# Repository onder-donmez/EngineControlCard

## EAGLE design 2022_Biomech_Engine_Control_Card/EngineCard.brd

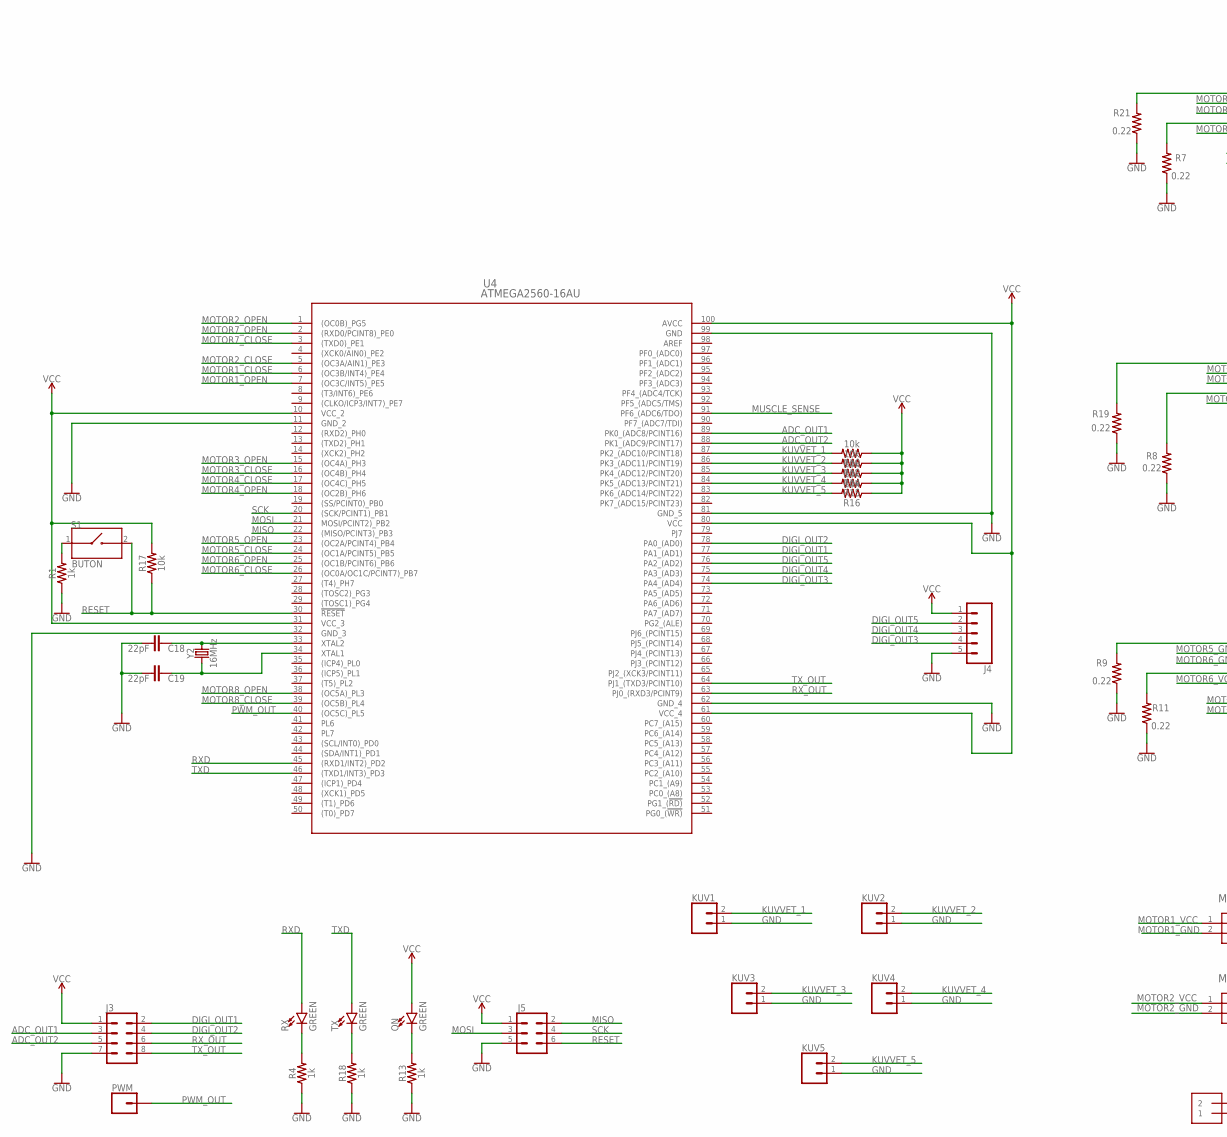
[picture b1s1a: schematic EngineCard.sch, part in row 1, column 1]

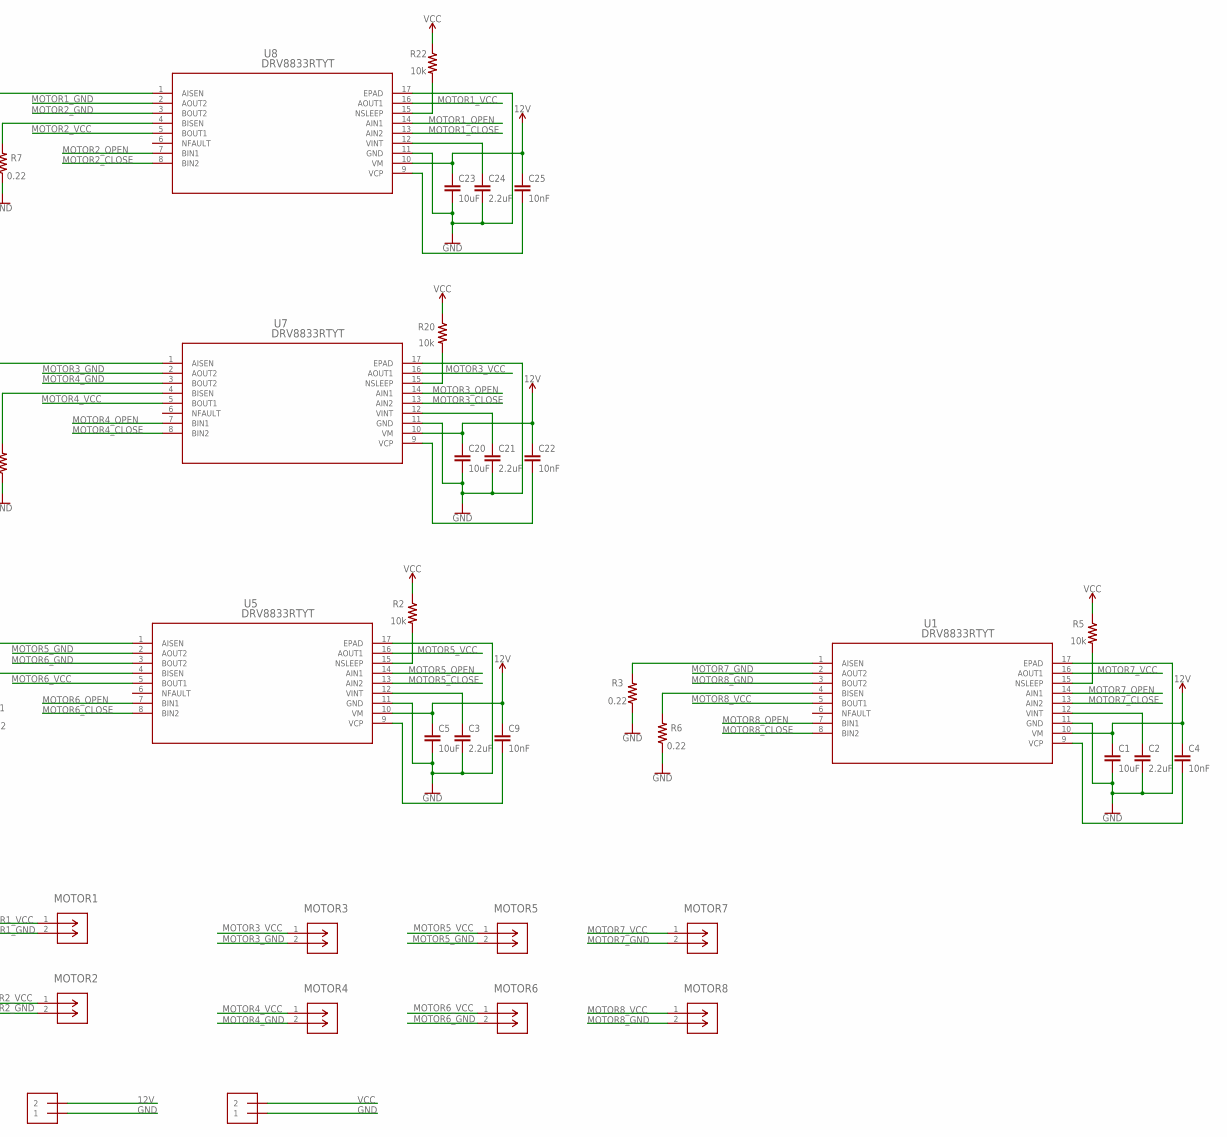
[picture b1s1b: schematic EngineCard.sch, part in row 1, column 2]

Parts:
C1, C5, C20, C23: 10uF; 0603
C2, C3, C21, C24: 2.2uF; 0603
C4, C9, C22, C25: 10nF; 0603
C18, C19: 22pF; 0603
J3: CONN_04X2; 2X4
J4: CONN_05NO_SILK; 1X05_NO_SILK
J5: CONN_03X2NO_SILK; 2X3-NS
KUV1, KUV2, KUV3, KUV4, KUV5: CONN_02; 1X02
MOTOR1, MOTOR2, MOTOR3, MOTOR4, MOTOR5, MOTOR6, MOTOR7, MOTOR8: 530470210; CON_530470210_MOL
ON: GREEN; LED-0603
PIL: 1X2-3.5MM
PWM: CONN_01; 1X01
R1, R4, R13, R18: 1k; 0603
R2, R5, R10, R12, R14, R15, R16, R17, R20, R22: 10k; 0603
R3, R6, R7, R8, R9, R11, R19, R21: 0.22; 0805
REG: 1X2-3.5MM
RX: GREEN; LED-0603
S1: BUTON; SW_1437566-4
TX: GREEN; LED-0603
U1, U5, U7, U8: DRV8833RTYT; RTY16
U4: ATMEGA2560-16AU; 100A_ATM
Y2: 16MHz; HC49US

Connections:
12V: C1.1, C4.1, C5.1, C9.1, C20.1, C22.1, C23.1, C25.1, PIL.2, U1.10 (VM), U5.10 (VM), U7.10 (VM), U8.10 (VM)
ADC_OUT1: J3.3, U4.89 (PK0_(ADC8/PCINT16))
ADC_OUT2: J3.5, U4.88 (PK1_(ADC9/PCINT17))
AREF: U4.98 (AREF)
DIGI_OUT1: J3.2, U4.77 (PA1_(AD1))
DIGI_OUT2: J3.4, U4.78 (PA0_(AD0))
DIGI_OUT3: J4.4, U4.74 (PA4_(AD4))
DIGI_OUT4: J4.3, U4.75 (PA3_(AD3))
DIGI_OUT5: J4.2, U4.76 (PA2_(AD2))
GND: C1.2, C2.2, C3.2, C5.2, C18.2, C19.2, C20.2, C21.2, C23.2, C24.2, J3.7, J4.5, J5.5, KUV1.1, KUV2.1, KUV3.1, KUV4.1, KUV5.1, PIL.1, R1.1, R3.1, R4.1, R6.1, R7.1, R8.1, R9.1, R11.1, R13.1, R18.1, R19.1, R21.1, REG.1, U1.11 (GND), U1.17 (EPAD), U4.11 (GND_2), U4.32 (GND_3), U4.62 (GND_4), U4.81 (GND_5), U4.99 (GND), U5.11 (GND), U5.17 (EPAD), U7.11 (GND), U7.17 (EPAD), U8.11 (GND), U8.17 (EPAD)
KUVVET_1: KUV1.2, R10.2, U4.87 (PK2_(ADC10/PCINT18))
KUVVET_2: KUV2.2, R12.2, U4.86 (PK3_(ADC11/PCINT19))
KUVVET_3: KUV3.2, R14.2, U4.85 (PK4_(ADC12/PCINT20))
KUVVET_4: KUV4.2, R15.2, U4.84 (PK5_(ADC13/PCINT21))
KUVVET_5: KUV5.2, R16.2, U4.83 (PK6_(ADC14/PCINT22))
MISO: J5.2, U4.22 ((MISO/PCINT3)_PB3)
MOSI: J5.3, U4.21 (MOSI/PCINT2)_PB2)
MOTOR1_CLOSE: U4.6 ((OC3B/INT4)_PE4), U8.13 (AIN2)
MOTOR1_GND: MOTOR1.2, U8.2 (AOUT2)
MOTOR1_OPEN: U4.7 ((OC3C/INT5)_PE5), U8.14 (AIN1)
MOTOR1_VCC: MOTOR1.1, U8.16 (AOUT1)
MOTOR2_CLOSE: U4.5 ((OC3A/AIN1)_PE3), U8.8 (BIN2)
MOTOR2_GND: MOTOR2.2, U8.3 (BOUT2)
MOTOR2_OPEN: U4.1 ((OC0B)_PG5), U8.7 (BIN1)
MOTOR2_VCC: MOTOR2.1, U8.5 (BOUT1)
MOTOR3_CLOSE: U4.16 ((OC4B)_PH4), U7.13 (AIN2)
MOTOR3_GND: MOTOR3.2, U7.2 (AOUT2)
MOTOR3_OPEN: U4.15 ((OC4A)_PH3), U7.14 (AIN1)
MOTOR3_VCC: MOTOR3.1, U7.16 (AOUT1)
MOTOR4_CLOSE: U4.17 ((OC4C)_PH5), U7.8 (BIN2)
MOTOR4_GND: MOTOR4.2, U7.3 (BOUT2)
MOTOR4_OPEN: U4.18 ((OC2B)_PH6), U7.7 (BIN1)
MOTOR4_VCC: MOTOR4.1, U7.5 (BOUT1)
MOTOR5_CLOSE: U4.24 ((OC1A/PCINT5)_PB5), U5.13 (AIN2)
MOTOR5_GND: MOTOR5.2, U5.2 (AOUT2)
MOTOR5_OPEN: U4.23 ((OC2A/PCINT4)_PB4), U5.14 (AIN1)
MOTOR5_VCC: MOTOR5.1, U5.16 (AOUT1)
MOTOR6_CLOSE: U4.26 ((OC0A/OC1C/PCINT7)_PB7), U5.8 (BIN2)
MOTOR6_GND: MOTOR6.2, U5.3 (BOUT2)
MOTOR6_OPEN: U4.25 ((OC1B/PCINT6)_PB6), U5.7 (BIN1)
MOTOR6_VCC: MOTOR6.1, U5.5 (BOUT1)
MOTOR7_CLOSE: U1.13 (AIN2), U4.3 ((TXD0)_PE1)
MOTOR7_GND: MOTOR7.2, U1.2 (AOUT2)
MOTOR7_OPEN: U1.14 (AIN1), U4.2 ((RXD0/PCINT8)_PE0)
MOTOR7_VCC: MOTOR7.1, U1.16 (AOUT1)
MOTOR8_CLOSE: U1.8 (BIN2), U4.39 ((OC5B)_PL4)
MOTOR8_GND: MOTOR8.2, U1.3 (BOUT2)
MOTOR8_OPEN: U1.7 (BIN1), U4.38 ((OC5A)_PL3)
MOTOR8_VCC: MOTOR8.1, U1.5 (BOUT1)
MUSCLE_SENSE: U4.91 (PF6_(ADC6/TDO))
unnamed: R9.2, U5.1 (AISEN)
unnamed: R1.2, S1.1
unnamed: R2.2, U5.15 (NSLEEP)
unnamed: C4.2, U1.9 (VCP)
unnamed: R3.2, U1.1 (AISEN)
unnamed: C2.1, U1.12 (VINT)
unnamed: R5.2, U1.15 (NSLEEP)
unnamed: C9.2, U5.9 (VCP)
unnamed: R6.2, U1.4 (BISEN)
unnamed: R7.2, U8.4 (BISEN)
unnamed: R8.2, U7.4 (BISEN)
unnamed: C3.1, U5.12 (VINT)
unnamed: R11.2, U5.4 (BISEN)
unnamed: R4.2, RX.C
unnamed: ON.C, R13.2
unnamed: R18.2, TX.C
unnamed: C18.1, U4.33 (XTAL2), Y2.2
unnamed: C19.1, U4.34 (XTAL1), Y2.1
unnamed: C22.2, U7.9 (VCP)
unnamed: R19.2, U7.1 (AISEN)
unnamed: C21.1, U7.12 (VINT)
unnamed: R20.2, U7.15 (NSLEEP)
unnamed: C25.2, U8.9 (VCP)
unnamed: R21.2, U8.1 (AISEN)
unnamed: C24.1, U8.12 (VINT)
unnamed: R22.2, U8.15 (NSLEEP)
PWM_OUT: PWM.1, U4.40 ((OC5C)_PL5)
RESET: J5.6, R17.1, S1.2, U4.30 (!RESET)
RXD: RX.A, U4.45 ((RXD1/INT2)_PD2)
RX_OUT: J3.6, U4.63 (PJ0_(RXD3/PCINT9))
SCK: J5.4, U4.20 ((SCK/PCINT1)_PB1)
TXD: TX.A, U4.46 ((TXD1/INT3)_PD3)
TX_OUT: J3.8, U4.64 (PJ1_(TXD3/PCINT10))
VCC: J3.1, J4.1, J5.1, ON.A, R2.1, R5.1, R10.1, R12.1, R14.1, R15.1, R16.1, R17.2, R20.1, R22.1, REG.2, U4.10 (VCC_2), U4.31 (VCC_3), U4.61 (VCC_4), U4.80 (VCC), U4.100 (AVCC)

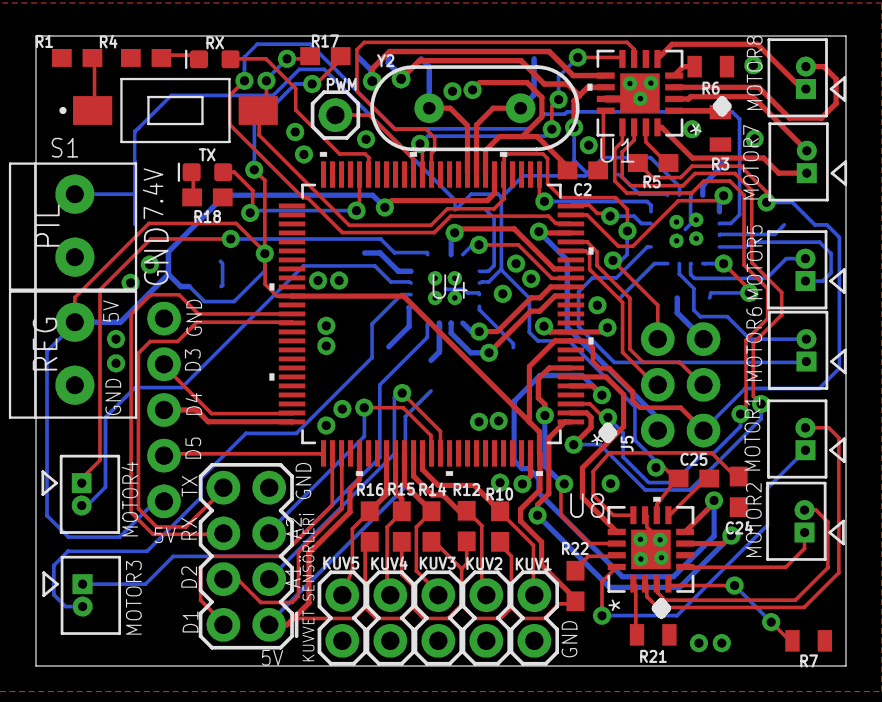
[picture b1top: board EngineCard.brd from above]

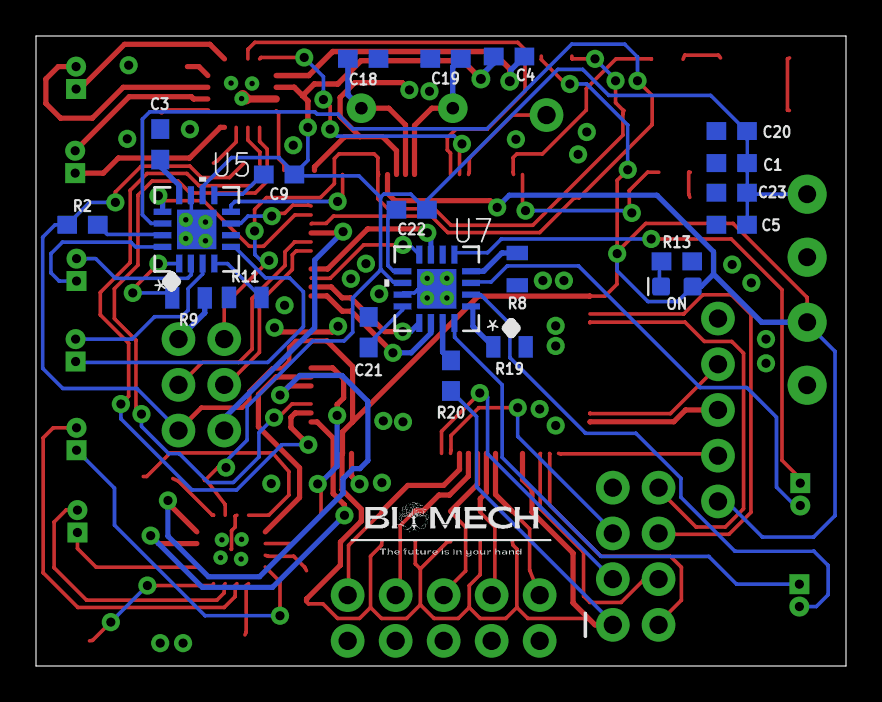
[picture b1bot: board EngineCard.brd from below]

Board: 2 copper layers, 45.0 x 35.0 mm, 65 parts (21 on the bottom side), 82 nets.

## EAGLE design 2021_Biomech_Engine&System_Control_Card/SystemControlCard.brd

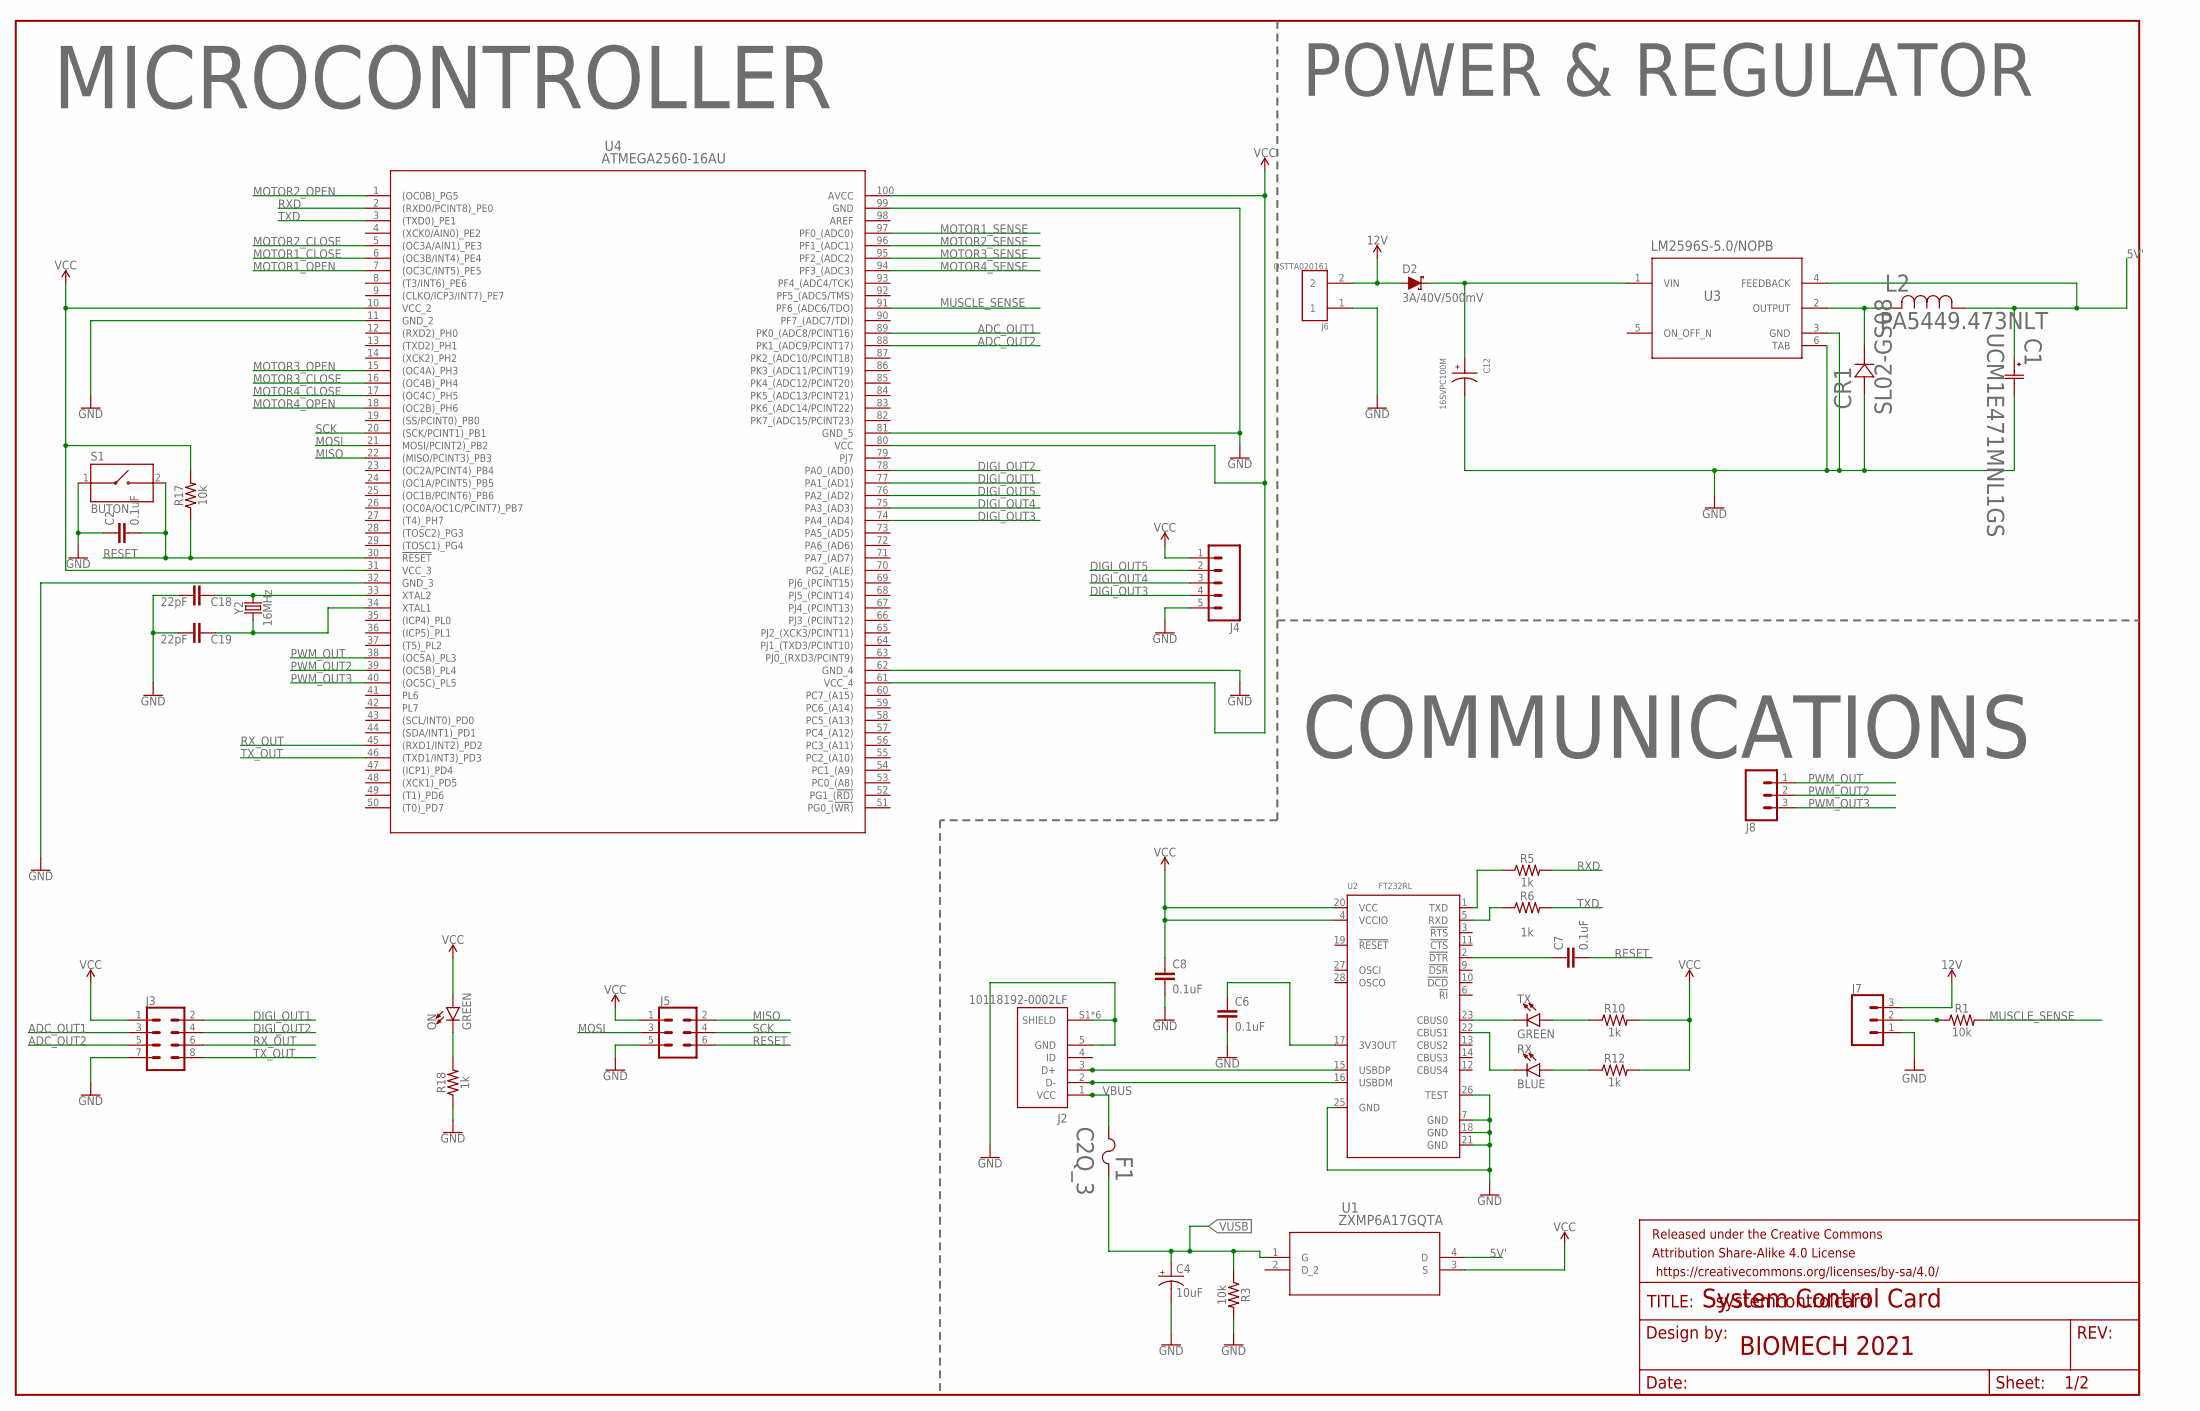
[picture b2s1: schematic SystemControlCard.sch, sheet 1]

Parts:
C1: UCM1E471MNL1GS; CAP_UCD_8X10_NCH
C2, C6, C7, C8: 0.1uF; 0603
C4: 10uF; EIA3216
C12: 16SVPC100M; CAP_16SVPC100M
C18, C19: 22pF; 0603
CR1: SL02-GS08; DIODE_SL02-GS08_VIS
D2: 3A/40V/500mV; SMA-DIODE
F1: C2Q_3; C2_BEL
FRAME2: FRAME-LEDGER; CREATIVE_COMMONS
J2: 10118192-0002LF; AMPHENOL_10118192-0002LF
J3: CONN_04X2; 2X4
J4: CONN_05NO_SILK; 1X05_NO_SILK
J5: CONN_03X2NO_SILK; 2X3-NS
J6: OSTTA020161; OST_OSTTA020161
J7, J8: CONN_031X03_NO_SILK; 1X03_NO_SILK
L2: PA5449.473NLT; IND_PA5449.473NLT_PUL
ON: GREEN; LED-0603
R1, R3, R17: 10k; 0603
R5, R6, R10, R12, R18: 1k; 0603
RX: BLUE; LED-0603
S1: BUTON; SW_1437566-4
TX: GREEN; LED-0603
U1: ZXMP6A17GQTA; SOT-223_DIO
U2: FT232RL; SSOP28-0.65-10.2X5.2MM
U3: LM2596S-5.0/NOPB; KTT0005B
U4: ATMEGA2560-16AU; 100A_ATM
Y2: 16MHz; HC49US

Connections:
5V': C1.1, L2.1, U1.4 (D), U3.4 (FEEDBACK)
12V: D2.A, J6.2, J7.3; also elsewhere on the board
ADC_OUT1: J3.3, U4.89 (PK0_(ADC8/PCINT16))
ADC_OUT2: J3.5, U4.88 (PK1_(ADC9/PCINT17))
AREF: U4.98 (AREF)
DIGI_OUT1: J3.2, U4.77 (PA1_(AD1))
DIGI_OUT2: J3.4, U4.78 (PA0_(AD0))
DIGI_OUT3: J4.4, U4.74 (PA4_(AD4))
DIGI_OUT4: J4.3, U4.75 (PA3_(AD3))
DIGI_OUT5: J4.2, U4.76 (PA2_(AD2))
GND: C1.2, C2.1, C4.-, C6.2, C8.2, C12.2, C18.2, C19.2, CR1.2, J2.5 (GND), J2.S1 (SHIELD), J2.S2 (SHIELD), J2.S3 (SHIELD), J2.S4 (SHIELD), J2.S5 (SHIELD), J2.S6 (SHIELD), J3.7, J4.5, J5.5, J6.1, J7.1, R3.2, R18.1, S1.1, U2.7 (GND), U2.18 (GND), U2.21 (GND), U2.25 (GND), U2.26 (TEST), U3.3 (GND), U3.6 (TAB), U4.11 (GND_2), U4.32 (GND_3), U4.62 (GND_4), U4.81 (GND_5), U4.99 (GND); also elsewhere on the board
MISO: J5.2, U4.22 ((MISO/PCINT3)_PB3)
MOSI: J5.3, U4.21 (MOSI/PCINT2)_PB2)
MOTOR1_CLOSE: U4.6 ((OC3B/INT4)_PE4); also elsewhere on the board
MOTOR1_OPEN: U4.7 ((OC3C/INT5)_PE5); also elsewhere on the board
MOTOR1_SENSE: U4.97 (PF0_(ADC0)); also elsewhere on the board
MOTOR2_CLOSE: U4.5 ((OC3A/AIN1)_PE3); also elsewhere on the board
MOTOR2_OPEN: U4.1 ((OC0B)_PG5); also elsewhere on the board
MOTOR2_SENSE: U4.96 (PF1_(ADC1)); also elsewhere on the board
MOTOR3_CLOSE: U4.16 ((OC4B)_PH4); also elsewhere on the board
MOTOR3_OPEN: U4.15 ((OC4A)_PH3); also elsewhere on the board
MOTOR3_SENSE: U4.95 (PF2_(ADC2)); also elsewhere on the board
MOTOR4_CLOSE: U4.17 ((OC4C)_PH5); also elsewhere on the board
MOTOR4_OPEN: U4.18 ((OC2B)_PH6); also elsewhere on the board
MOTOR4_SENSE: U4.94 (PF3_(ADC3)); also elsewhere on the board
MUSCLE_SENSE: R1.2, U4.91 (PF6_(ADC6/TDO))
unnamed: C12.1, D2.C, U3.1 (VIN)
unnamed: J2.3 (D+), U2.15 (USBDP)
unnamed: J2.2 (D-), U2.16 (USBDM)
unnamed: R5.1, U2.1 (TXD)
unnamed: R6.1, U2.5 (RXD)
unnamed: C6.1, U2.17 (3V3OUT)
unnamed: TX.C, U2.23 (CBUS0)
unnamed: RX.C, U2.22 (CBUS1)
unnamed: J7.2, R1.1
unnamed: R10.1, TX.A
unnamed: R12.1, RX.A
unnamed: C7.1, U2.2 (!DTR)
unnamed: CR1.1, L2.2, U3.2 (OUTPUT)
unnamed: ON.C, R18.2
unnamed: C18.1, U4.33 (XTAL2), Y2.2
unnamed: C19.1, U4.34 (XTAL1), Y2.1
PWM_OUT: J8.1, U4.38 ((OC5A)_PL3)
PWM_OUT2: J8.2, U4.39 ((OC5B)_PL4)
PWM_OUT3: J8.3, U4.40 ((OC5C)_PL5)
RESET: C2.2, C7.2, J5.6, R17.1, S1.2, U4.30 (!RESET)
RXD: R5.2, U4.2 ((RXD0/PCINT8)_PE0)
RX_OUT: J3.6, U4.45 ((RXD1/INT2)_PD2)
SCK: J5.4, U4.20 ((SCK/PCINT1)_PB1)
TXD: R6.2, U4.3 ((TXD0)_PE1)
TX_OUT: J3.8, U4.46 ((TXD1/INT3)_PD3)
VBUS: F1.1, J2.1 (VCC)
VCC: C8.1, J3.1, J4.1, J5.1, ON.A, R10.2, R12.2, R17.2, U1.3 (S), U2.4 (VCCIO), U2.20 (VCC), U4.10 (VCC_2), U4.31 (VCC_3), U4.61 (VCC_4), U4.80 (VCC), U4.100 (AVCC); also elsewhere on the board
VUSB: C4.+, F1.2, R3.1, U1.1 (G)

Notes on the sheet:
MICROCONTROLLER
POWER & REGULATOR
COMMUNICATIONS

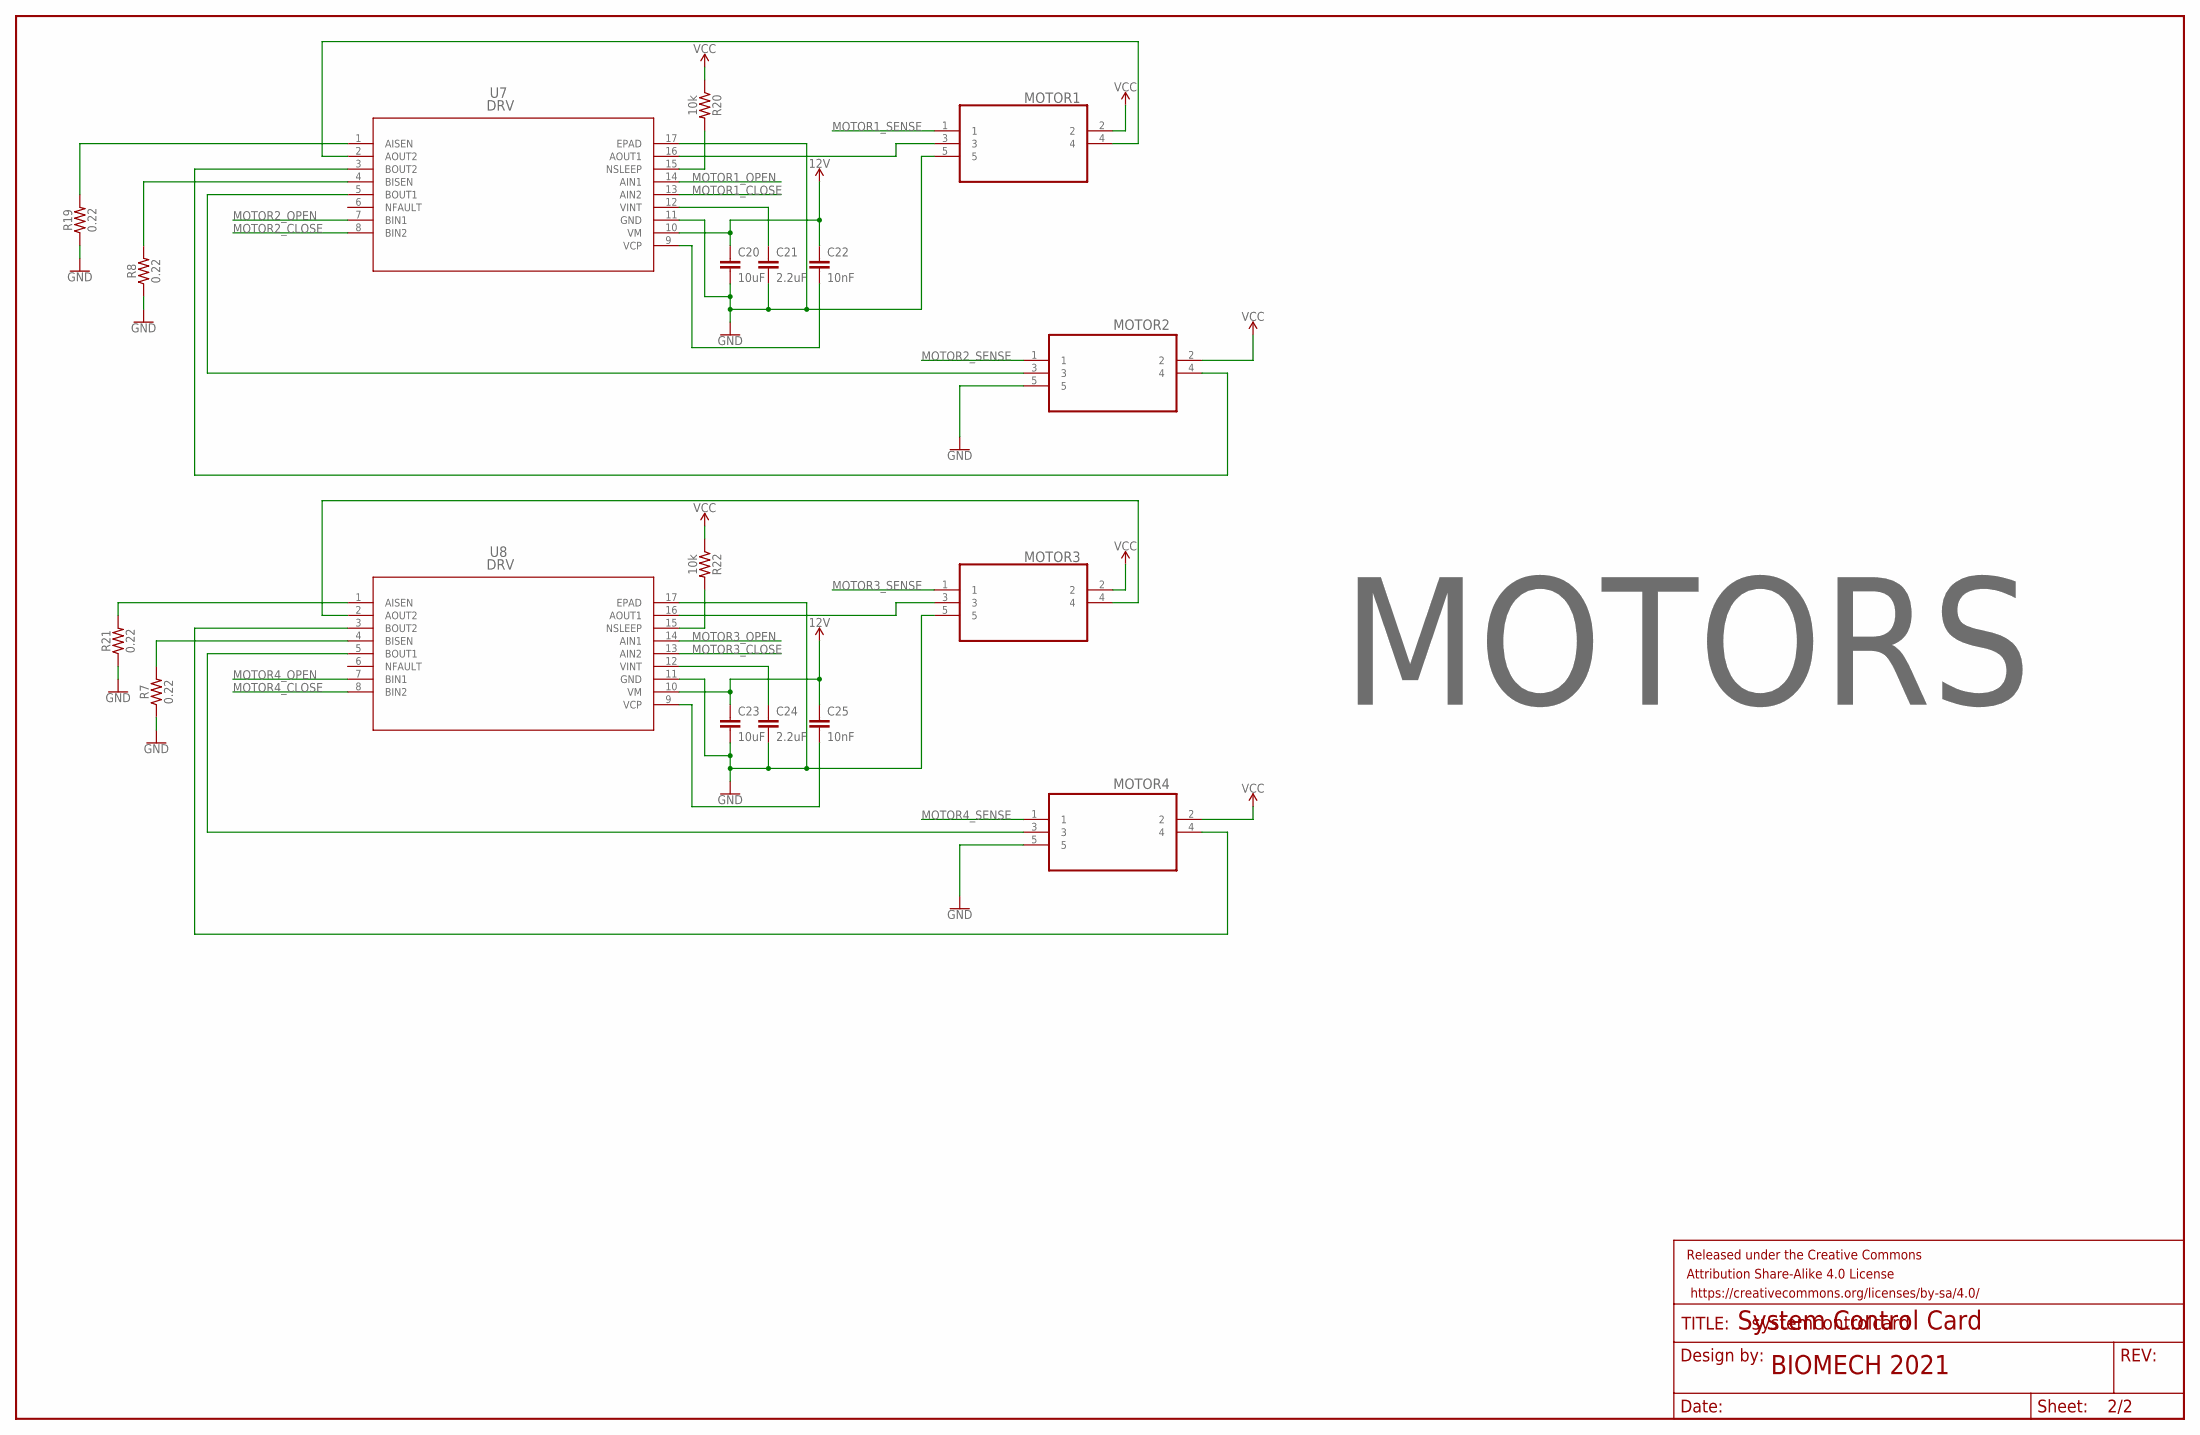
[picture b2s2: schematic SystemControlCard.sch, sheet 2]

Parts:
C20, C23: 10uF; 0603
C21, C24: 2.2uF; 0603
C22, C25: 10nF; 0603
FRAME1: FRAME-LEDGER; CREATIVE_COMMONS
MOTOR1, MOTOR2, MOTOR3, MOTOR4: SFW5R-1STE1LF; FCI_SFW5R-1STE1LF
R7, R8, R19, R21: 0.22; 0805
R20, R22: 10k; 0603
U7, U8: DRV; RTY16

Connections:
12V: C20.1, C22.1, C23.1, C25.1, U7.10 (VM), U8.10 (VM); also elsewhere on the board
GND: C20.2, C21.2, C23.2, C24.2, MOTOR1.5, MOTOR2.5, MOTOR3.5, MOTOR4.5, R7.1, R8.1, R19.1, R21.1, U7.11 (GND), U7.17 (EPAD), U8.11 (GND), U8.17 (EPAD); also elsewhere on the board
MOTOR1_CLOSE: U7.13 (AIN2); also elsewhere on the board
MOTOR1_OPEN: U7.14 (AIN1); also elsewhere on the board
MOTOR1_SENSE: MOTOR1.1; also elsewhere on the board
MOTOR2_CLOSE: U7.8 (BIN2); also elsewhere on the board
MOTOR2_OPEN: U7.7 (BIN1); also elsewhere on the board
MOTOR2_SENSE: MOTOR2.1; also elsewhere on the board
MOTOR3_CLOSE: U8.13 (AIN2); also elsewhere on the board
MOTOR3_OPEN: U8.14 (AIN1); also elsewhere on the board
MOTOR3_SENSE: MOTOR3.1; also elsewhere on the board
MOTOR4_CLOSE: U8.8 (BIN2); also elsewhere on the board
MOTOR4_OPEN: U8.7 (BIN1); also elsewhere on the board
MOTOR4_SENSE: MOTOR4.1; also elsewhere on the board
unnamed: R7.2, U8.4 (BISEN)
unnamed: R8.2, U7.4 (BISEN)
unnamed: C22.2, U7.9 (VCP)
unnamed: R19.2, U7.1 (AISEN)
unnamed: C21.1, U7.12 (VINT)
unnamed: MOTOR2.3, U7.5 (BOUT1)
unnamed: MOTOR1.4, U7.2 (AOUT2)
unnamed: MOTOR2.4, U7.3 (BOUT2)
unnamed: MOTOR1.3, U7.16 (AOUT1)
unnamed: R20.2, U7.15 (NSLEEP)
unnamed: C25.2, U8.9 (VCP)
unnamed: R21.2, U8.1 (AISEN)
unnamed: C24.1, U8.12 (VINT)
unnamed: MOTOR4.3, U8.5 (BOUT1)
unnamed: MOTOR3.4, U8.2 (AOUT2)
unnamed: MOTOR4.4, U8.3 (BOUT2)
unnamed: MOTOR3.3, U8.16 (AOUT1)
unnamed: R22.2, U8.15 (NSLEEP)
VCC: MOTOR1.2, MOTOR2.2, MOTOR3.2, MOTOR4.2, R20.1, R22.1; also elsewhere on the board

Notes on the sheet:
MOTORS

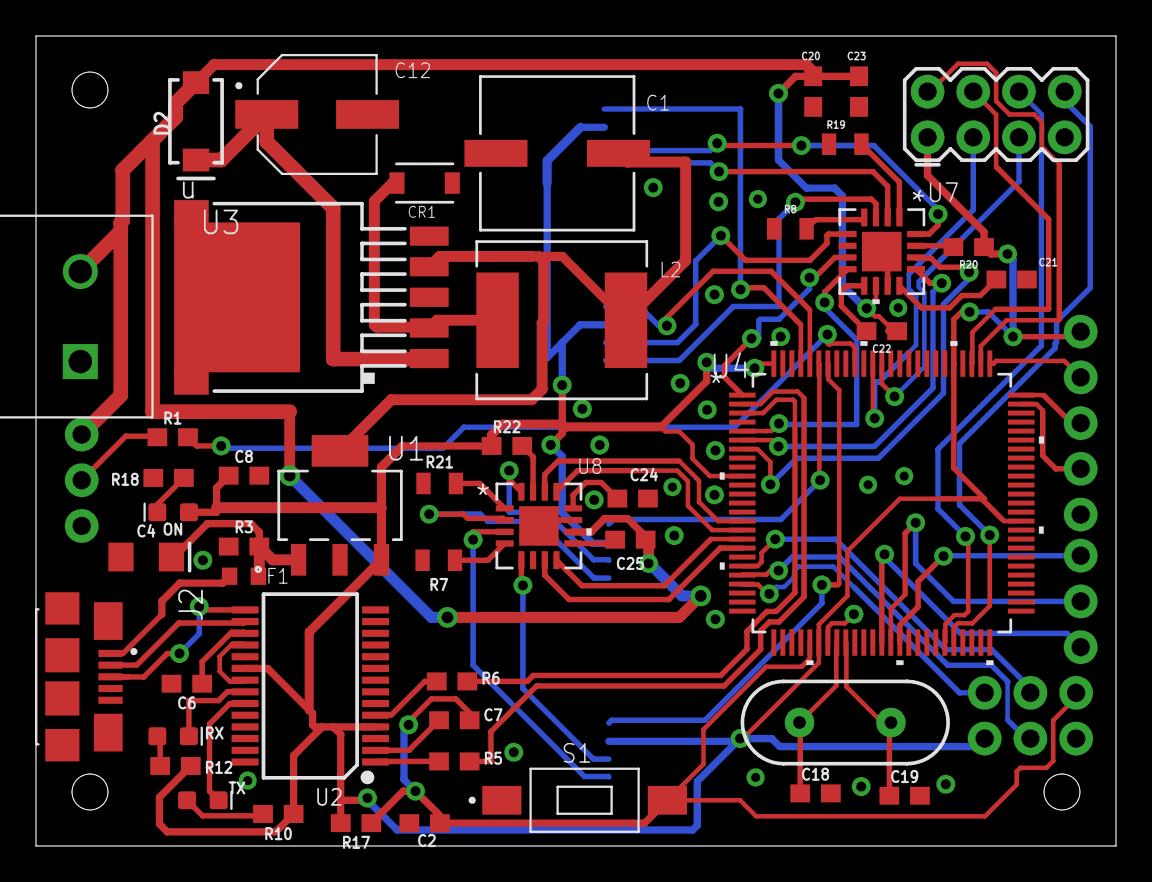
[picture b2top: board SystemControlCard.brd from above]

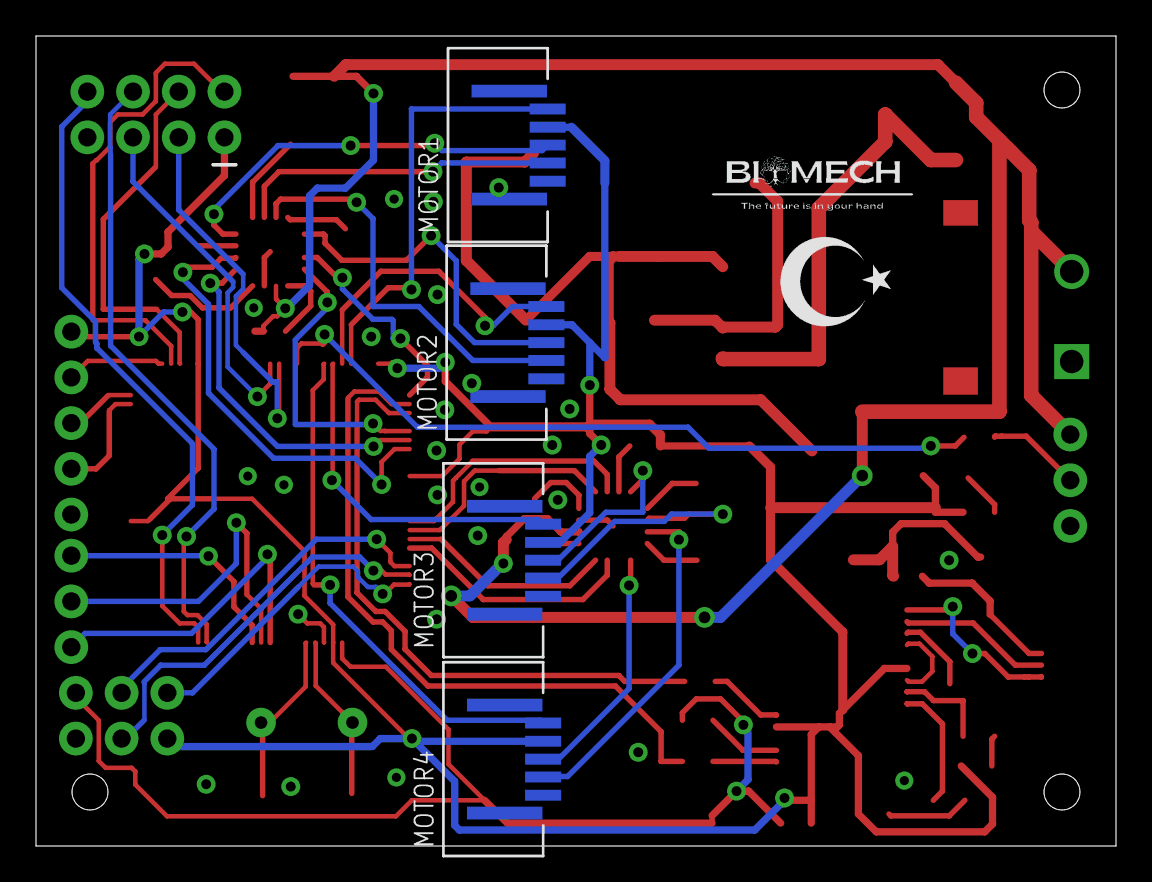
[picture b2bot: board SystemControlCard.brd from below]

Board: 2 copper layers, 60.0 x 45.0 mm, 58 parts (5 on the bottom side), 71 nets.

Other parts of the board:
U$1: TR_MINI

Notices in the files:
parts and their libraries:
SparkFun-Capacitors: Licensing: Creative Commons ShareAlike 4.0 International - https://creativecommons.org/licenses/by-sa/4.0
SparkFun-Aesthetics: Released under the Creative Commons Attribution Share-Alike 4.0 License
SparkFun-Aesthetics: https://creativecommons.org/licenses/by-sa/4.0
